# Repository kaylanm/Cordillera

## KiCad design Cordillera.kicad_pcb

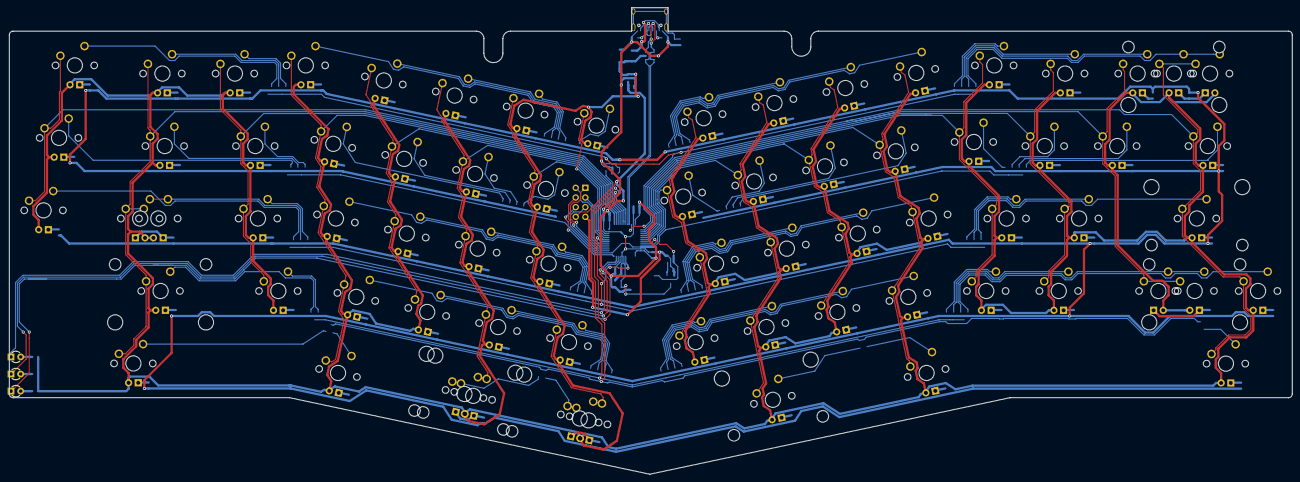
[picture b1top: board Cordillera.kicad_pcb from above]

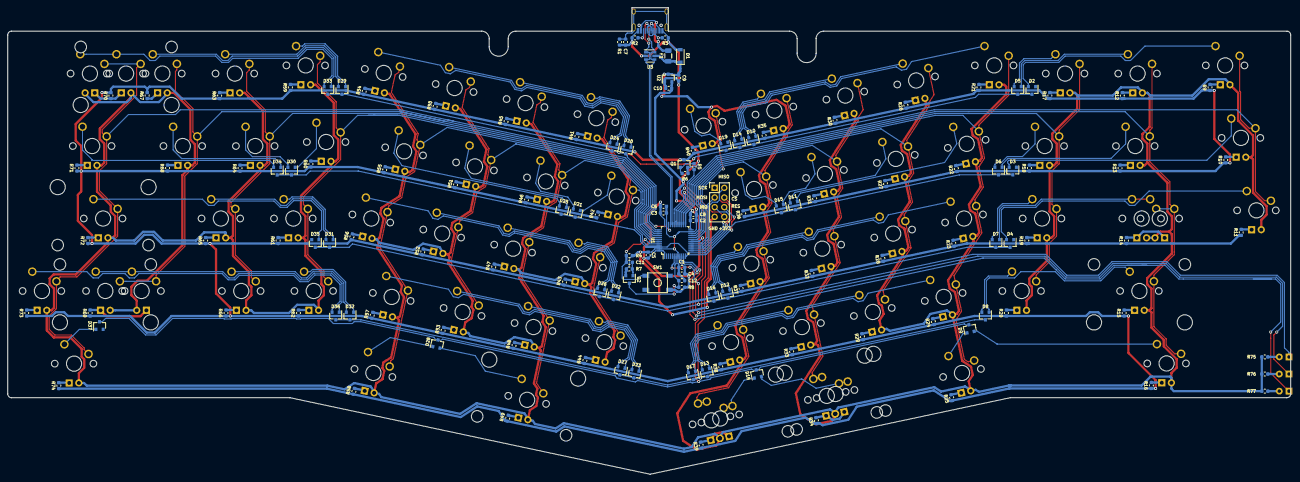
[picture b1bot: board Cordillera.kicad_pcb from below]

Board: 2 copper layers, 337.2 x 122.6 mm, 209 parts (135 on the bottom side), 180 nets.

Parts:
C1: 10n; C_0603_1608Metric
C2, C3, C5: 100n; C_0603_1608Metric
C4, C9, C10, C12: 1u; C_0603_1608Metric
C6, C8, C11: 4.7u; C_0603_1608Metric
C7: 4.7n; C_0603_1608Metric
D1: SMF6.0CA; D_SOD-123
D2, D3, D4, D5, D6, D7, D8, D9, D10, D11, D12, D13, D14, D15, D16, D17, D18, D19, D20, D21, D22, D23, D24, D25, D26, D27, D28, D29, D30, D31, D32, D33, D34, D35, D36, D37: BAV70; SOT-23
D38: LED 1; LED_D3.0mm
D39: LED 2; LED_D3.0mm
D40: LED 3; LED_D3.0mm
F1: 1A; Fuse_1206_3216Metric
J1: Conn_01x08; PinHeader_2x04_P2.54mm_Vertical
KBA1, KBA2, KBA3: Keyboard_Switch; MXOnly-1U
KBB1: Keyboard_Switch; MXOnly-1U
KBB2, KBB5: Keyboard_Switch; MXOnly-1.5U
KBB3: Keyboard_Switch; MXOnly-1.75U
KBB3-1: Keyboard_Switch; MXOnly-1.25U-FLIPPED
KBB4: Keyboard_Switch; MXOnly-2.25U
KBC1, KBC2, KBC3, KBC4: Keyboard_Switch; MXOnly-1U
KBD1, KBD2, KBD3, KBD4: Keyboard_Switch; MXOnly-1U
KBD5: Keyboard_Switch; MXOnly-1.5U
KBE1, KBE2, KBE3, KBE4: Keyboard_Switch; MXOnly-1U
KBF1, KBF2, KBF3, KBF4: Keyboard_Switch; MXOnly-1U
KBF5: Keyboard_Switch; MXOnly-2U-FLIPPED-ReversedStabilizers
KBF5-1: Keyboard_Switch; MXOnly-2.25U-ReversedStabilizers
KBG1, KBG2, KBG3, KBG4, KBG5-1: Keyboard_Switch; MXOnly-1U
KBG5: Keyboard_Switch; MXOnly-1.25U-FLIPPED
KBH1: Keyboard_Switch; MXOnly-1U
KBI1, KBI2, KBI3, KBI4: Keyboard_Switch; MXOnly-1U
KBJ1, KBJ2, KBJ3, KBJ4: Keyboard_Switch; MXOnly-1U
KBJ5: Keyboard_Switch; MXOnly-2.75U-ReversedStabilizers
KBK1, KBK2, KBK3, KBK4: Keyboard_Switch; MXOnly-1U
KBL1, KBL2, KBL3, KBL4: Keyboard_Switch; MXOnly-1U
KBL5: Keyboard_Switch; MXOnly-1.5U
KBM1, KBM2, KBM3, KBM4: Keyboard_Switch; MXOnly-1U
KBN1, KBN2, KBN3, KBN4: Keyboard_Switch; MXOnly-1U
KBO1, KBO2: Keyboard_Switch; MXOnly-1U
KBO4: Keyboard_Switch; MXOnly-2.75U
KBO4-1: Keyboard_Switch; MXOnly-1.75U-FLIPPED
KBP1: Keyboard_Switch; MXOnly-2U
KBP1-1: Keyboard_Switch; MXOnly-1U-FLIPPED
KBP2, KBP5: Keyboard_Switch; MXOnly-1.5U
KBP3: Keyboard_Switch; MXOnly-2.25U-ReversedStabilizers
KBP4: Keyboard_Switch; MXOnly-1U
Q1, Q2: 2N7002; SOT-23
R1: 1M; R_0603_1608Metric
R2, R3: 5.1k; R_0603_1608Metric
R4, R6, R8: 10k; R_0603_1608Metric
R5, R9, R10, R11, R12, R13, R14, R15, R16, R17, R18, R19, R20, R21, R22, R23, R24, R25, R26, R27, R28, R29, R30, R31, R32, R33, R34, R35, R36, R37, R38, R39, R40, R41, R42, R43, R44, R45, R46, R47, R48, R49, R50, R51, R52, R53, R54, R55, R56, R57, R58, R59, R60, R61, R62, R63, R64, R65, R66, R67, R68, R69, R70, R71, R72, R73, R74, R75, R76, R77: 470; R_0603_1608Metric
R7: 100k; R_0603_1608Metric
SW1: SW_SPST; TactSwitch_SPST_5.1x5.1mm
U1: STM32F072CBTx; LQFP-48_7x7mm_P0.5mm
U2: XC6206P332MR; SOT-23
U3: SRV05-4; SOT-23-6
USB1: HRO-TYPE-C-31-M-12

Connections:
+3V3: C1.2, C2.2, C3.2, C4.2, C5.2, C6.2, C8.2, C10.2, J1.8, R8.2, SW1.2, U1.1, U1.9, U1.24, U1.36, U1.48, U2.2
+5V: C9.2, D1.1, F1.1, KBA1.3, KBA2.3, KBA3.3, KBB1.3, KBB2.3, KBB3.3, KBB3-1.3, KBB4.3, KBB5.3, KBC1.3, KBC2.3, KBC3.3, KBC4.3, KBD1.3, KBD2.3, KBD3.3, KBD4.3, KBD5.3, KBE1.3, KBE2.3, KBE3.3, KBE4.3, KBF1.3, KBF2.3, KBF3.3, KBF4.3, KBF5.3, KBF5-1.3, KBG1.3, KBG2.3, KBG3.3, KBG4.3, KBG5.3, KBG5-1.3, KBH1.3, KBI1.3, KBI2.3, KBI3.3, KBI4.3, KBJ1.3, KBJ2.3, KBJ3.3, KBJ4.3, KBJ5.3, KBK1.3, KBK2.3, KBK3.3, KBK4.3, KBL1.3, KBL2.3, KBL3.3, KBL4.3, KBL5.3, KBM1.3, KBM2.3, KBM3.3, KBM4.3, KBN1.3, KBN2.3, KBN3.3, KBN4.3, KBO1.3, KBO2.3, KBO4.3, KBO4-1.3, KBP1.3, KBP1-1.3, KBP2.3, KBP3.3, KBP4.3, KBP5.3, R75.2, R76.2, R77.2, U2.3, U3.5
/A0: D40.1, U1.10
/A1: D39.1, U1.11
/A9: D9.3, D18.3, D28.3, D37.3, U1.30
/A10: D8.3, D13.3, D17.3, D23.3, D27.3, D32.3, D36.3, U1.31
/A15: KBO1.1, KBO2.1, KBO4.1, KBO4-1.1, U1.38
/B0: D38.1, U1.18
/B1: KBH1.1, U1.19
/B2: KBG1.1, KBG2.1, KBG3.1, KBG4.1, KBG5.2, KBG5-1.2, U1.20
/B3: KBN1.1, KBN2.1, KBN3.1, KBN4.1, U1.39
/B4: KBM1.1, KBM2.1, KBM3.1, KBM4.1, U1.40
/B5: KBL1.1, KBL2.1, KBL3.1, KBL4.1, KBL5.1, U1.41
/B6: KBK1.1, KBK2.1, KBK3.1, KBK4.1, U1.42
/B7: KBJ1.1, KBJ2.1, KBJ3.1, KBJ4.1, KBJ5.1, U1.43
/B8: KBI1.1, KBI2.1, KBI3.1, KBI4.1, U1.45
/B9: D3.3, D6.3, D11.3, D15.3, D21.3, D25.3, D30.3, D34.3, U1.46
/B10: KBF1.1, KBF2.1, KBF3.1, KBF4.1, KBF5.2, KBF5-1.2, U1.21
/B11: KBE1.1, KBE2.1, KBE3.1, KBE4.1, U1.22
/B12: KBD1.1, KBD2.1, KBD3.1, KBD4.1, KBD5.1, U1.25
/B13: KBC1.1, KBC2.1, KBC3.1, KBC4.1, U1.26
/B14: KBB1.1, KBB2.1, KBB3.1, KBB3-1.1, KBB4.1, KBB5.1, U1.27
/B15: KBA1.1, KBA2.1, KBA3.1, U1.28
/BOOT0: C11.1, R4.1, SW1.1, U1.44
/D+: U1.33, U3.1, U3.3, USB1.6, USB1.8
/D-: U1.32, U3.4, U3.6, USB1.5, USB1.7
/F1: D4.3, D7.3, D12.3, D16.3, D22.3, D26.3, D31.3, D35.3, U1.6
/LED_GND: Q1.3, R9.1, R10.1, R11.1, R12.1, R13.1, R14.1, R15.1, R16.1, R17.1, R18.1, R19.1, R20.1, R21.1, R22.1, R23.1, R24.1, R25.1, R26.1, R27.1, R28.1, R29.1, R30.1, R31.1, R32.1, R33.1, R34.1, R35.1, R36.1, R37.1, R38.1, R39.1, R40.1, R41.1, R42.1, R43.1, R44.1, R45.1, R46.1, R47.1, R48.1, R49.1, R50.1, R51.1, R52.1, R53.1, R54.1, R55.1, R56.1, R57.1, R58.1, R59.1, R60.1, R61.1, R62.1, R63.1, R64.1, R65.1, R66.1, R67.2, R68.1, R69.1, R70.2, R71.1, R72.1, R73.1, R74.1
/LED_PWM: R5.2, U1.29
/NRST: C12.1, Q2.3, R8.1, U1.7
/SPI_CS: J1.4, U1.14
/SPI_IRQ: J1.5, U1.13
/SPI_MISO: J1.2, U1.16
/SPI_MOSI: J1.3, U1.17
/SPI_RES: J1.6, U1.12
/SPI_SCK: J1.1, U1.15
/SWDCLK: KBP1.1, KBP1-1.1, KBP2.1, KBP3.1, KBP4.1, KBP5.1, U1.37
/SWDIO: D2.3, D5.3, D10.3, D14.3, D19.3, D20.3, D24.3, D29.3, D33.3, U1.34
GND: C1.1, C2.1, C3.1, C4.1, C5.1, C6.1, C7.2, C8.1, C9.1, C10.1, C12.2, D1.2, J1.7, Q1.2, Q2.2, R1.1, R2.2, R3.1, R4.2, R6.2, R7.2, U1.8, U1.23, U1.35, U1.47, U2.1, U3.2, USB1.1, USB1.12
unnamed: C7.1, R1.2, USB1.13
unnamed: C11.2, Q2.1, R7.1
unnamed: D2.2, KBA1.2
unnamed: D3.2, KBA2.2
unnamed: D4.2, KBA3.2
unnamed: D5.1, KBB1.2
unnamed: D5.2, KBC1.2
unnamed: D6.1, KBB2.2
unnamed: D6.2, KBC2.2
unnamed: D7.1, KBB3.2, KBB3-1.2
unnamed: D7.2, KBC3.2
unnamed: D8.1, KBB4.2
unnamed: D8.2, KBC4.2
unnamed: D9.1, KBD5.2
unnamed: D9.2, KBB5.2
unnamed: D10.1, KBD1.2
unnamed: D10.2, KBE1.2
unnamed: D11.1, KBD2.2
unnamed: D11.2, KBE2.2
unnamed: D12.1, KBD3.2
unnamed: D12.2, KBE3.2
unnamed: D13.1, KBD4.2
unnamed: D13.2, KBE4.2
unnamed: D14.1, KBF1.2
unnamed: D14.2, KBG1.2
unnamed: D15.1, KBF2.2
unnamed: D15.2, KBG2.2
unnamed: D16.1, KBF3.2
unnamed: D16.2, KBG3.2
unnamed: D17.1, KBF4.2
unnamed: D17.2, KBG4.2
unnamed: D18.1, KBG5.1, KBG5-1.1
unnamed: D18.2, KBF5.1, KBF5-1.1
unnamed: D19.2, KBH1.2
unnamed: D20.1, KBI1.2
unnamed: D20.2, KBJ1.2
unnamed: D21.1, KBI2.2
unnamed: D21.2, KBJ2.2
unnamed: D22.1, KBI3.2
unnamed: D22.2, KBJ3.2
unnamed: D23.1, KBI4.2
unnamed: D23.2, KBJ4.2
unnamed: D24.1, KBK1.2
unnamed: D24.2, KBL1.2
unnamed: D25.1, KBK2.2
unnamed: D25.2, KBL2.2
unnamed: D26.1, KBK3.2
unnamed: D26.2, KBL3.2
unnamed: D27.1, KBK4.2
unnamed: D27.2, KBL4.2
unnamed: D28.1, KBL5.2
unnamed: D28.2, KBJ5.2
unnamed: D29.1, KBM1.2
unnamed: D29.2, KBN1.2
unnamed: D30.1, KBM2.2
unnamed: D30.2, KBN2.2
unnamed: D31.1, KBM3.2
unnamed: D31.2, KBN3.2
unnamed: D32.1, KBM4.2
unnamed: D32.2, KBN4.2
unnamed: D33.1, KBO1.2
unnamed: D33.2, KBP1.2, KBP1-1.2
unnamed: D34.1, KBO2.2
unnamed: D34.2, KBP2.2
unnamed: D35.1, KBP3.2
unnamed: D36.1, KBO4.2, KBO4-1.2
unnamed: D36.2, KBP4.2
unnamed: D37.1, KBP5.2
unnamed: D38.2, R75.1
unnamed: D39.2, R76.1
unnamed: D40.2, R77.1
unnamed: KBA1.4, R9.2
unnamed: KBA2.4, R10.2
unnamed: KBA3.4, R11.2
unnamed: KBB1.4, R12.2
unnamed: KBB2.4, R13.2
unnamed: KBB3.4, KBB3-1.4, R14.2
unnamed: KBB4.4, R15.2
unnamed: KBB5.4, R16.2
unnamed: KBC1.4, R17.2
unnamed: KBC2.4, R18.2
unnamed: KBC3.4, R19.2
unnamed: KBC4.4, R20.2
unnamed: KBD1.4, R21.2
unnamed: KBD2.4, R22.2
unnamed: KBD3.4, R23.2
unnamed: KBD4.4, R24.2
unnamed: KBD5.4, R25.2
unnamed: KBE1.4, R26.2
unnamed: KBE2.4, R27.2
unnamed: KBE3.4, R28.2
unnamed: KBE4.4, R29.2
unnamed: KBF1.4, R30.2
unnamed: KBF2.4, R31.2
unnamed: KBF3.4, R32.2
unnamed: KBF4.4, R33.2
unnamed: KBF5.4, KBF5-1.4, R34.2
unnamed: KBG1.4, R35.2
unnamed: KBG2.4, R36.2
unnamed: KBG3.4, R37.2
unnamed: KBG4.4, R38.2
unnamed: KBG5.4, KBG5-1.4, R39.2
unnamed: KBH1.4, R40.2
unnamed: KBI1.4, R41.2
unnamed: KBI2.4, R42.2
unnamed: KBI3.4, R43.2
unnamed: KBI4.4, R44.2
unnamed: KBJ1.4, R45.2
unnamed: KBJ2.4, R46.2
unnamed: KBJ3.4, R47.2
unnamed: KBJ4.4, R48.2
unnamed: KBJ5.4, R49.2
unnamed: KBK1.4, R50.2
unnamed: KBK2.4, R51.2
unnamed: KBK3.4, R52.2
unnamed: KBK4.4, R53.2
unnamed: KBL1.4, R54.2
unnamed: KBL2.4, R55.2
unnamed: KBL3.4, R56.2
unnamed: KBL4.4, R57.2
unnamed: KBL5.4, R58.2
unnamed: KBM1.4, R59.2
unnamed: KBM2.4, R60.2
unnamed: KBM3.4, R61.2
unnamed: KBM4.4, R62.2
unnamed: KBN1.4, R63.2
unnamed: KBN2.4, R64.2
unnamed: KBN3.4, R65.2
unnamed: KBN4.4, R66.2
unnamed: KBO1.4, R67.1
unnamed: KBO2.4, R68.2
unnamed: KBO4.4, KBO4-1.4, R69.2
unnamed: KBP1.4, KBP1-1.4, R70.1
unnamed: KBP2.4, R71.2
unnamed: KBP3.4, R72.2
unnamed: KBP4.4, R73.2
unnamed: KBP5.4, R74.2
unnamed: Q1.1, R5.1, R6.1
unnamed: R2.1, USB1.10
unnamed: R3.2, USB1.4
VBUS: F1.2, USB1.2, USB1.11

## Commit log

2021-03-28 Switch to bottom-mount USB-C.
